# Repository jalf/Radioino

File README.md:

Radioino
========

My components for an arduino-based home automation

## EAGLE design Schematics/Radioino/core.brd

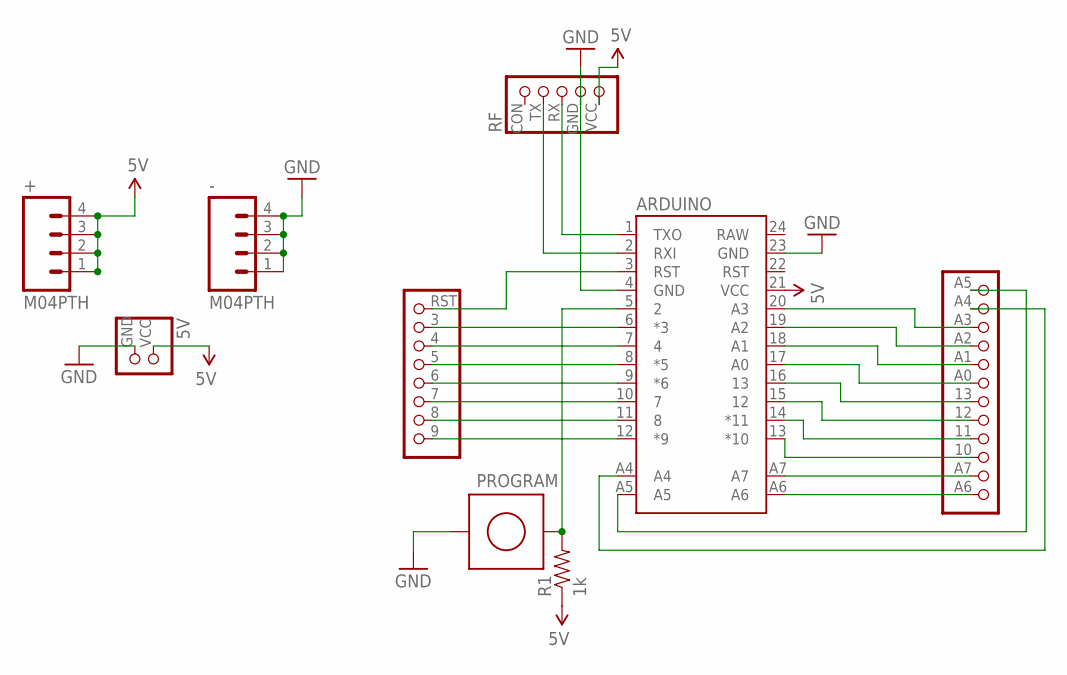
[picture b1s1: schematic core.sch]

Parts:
5V: DCPINHD-1X2; 1X02
+: M04PTH; 1X04
-: M04PTH; 1X04
ARDUINO: ARDUINO_PRO_MINI
PROGRAM: PUSHBUTTON
R1: 1k; AXIAL-0.1
RF: RFPINHD-1X5; 1X05
U$1: RIGHTPINHD-1X12; 1X12
U$2: LEFTPINHD-1X8; 1X08

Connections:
5V: 5V.VCC (1), +.1, +.2, +.3, +.4, ARDUINO.21 (VCC), R1.P$1 (1), RF.VCC (5)
GND: 5V.GND (2), -.1, -.2, -.3, -.4, ARDUINO.4 (GND), ARDUINO.23 (GND), PROGRAM.P$1, RF.GND (4)
unnamed: ARDUINO.A7, U$1.A7 (2)
unnamed: ARDUINO.A6, U$1.A6 (1)
unnamed: ARDUINO.13 (*10), U$1.10 (3)
unnamed: ARDUINO.14 (*11), U$1.11 (4)
unnamed: ARDUINO.15 (12), U$1.12 (5)
unnamed: ARDUINO.16 (13), U$1.13 (6)
unnamed: ARDUINO.17 (A0), U$1.A0 (7)
unnamed: ARDUINO.18 (A1), U$1.A1 (8)
unnamed: ARDUINO.19 (A2), U$1.A2 (9)
unnamed: ARDUINO.20 (A3), U$1.A3 (10)
unnamed: ARDUINO.A5, U$1.A5 (A7)
unnamed: ARDUINO.A4, U$1.A4 (11)
unnamed: ARDUINO.1 (TXO), RF.RX (3)
unnamed: ARDUINO.2 (RXI), RF.TX (2)
unnamed: ARDUINO.12 (*9), U$2.9 (1)
unnamed: ARDUINO.11 (8), U$2.8 (2)
unnamed: ARDUINO.10 (7), U$2.7 (3)
unnamed: ARDUINO.9 (*6), U$2.6 (4)
unnamed: ARDUINO.8 (*5), U$2.5
unnamed: ARDUINO.7 (4), U$2.4 (6)
unnamed: ARDUINO.6 (*3), U$2.3 (7)
unnamed: ARDUINO.3 (RST), U$2.RST (8)
unnamed: ARDUINO.5 (2), PROGRAM.P$2, R1.P$2 (2)

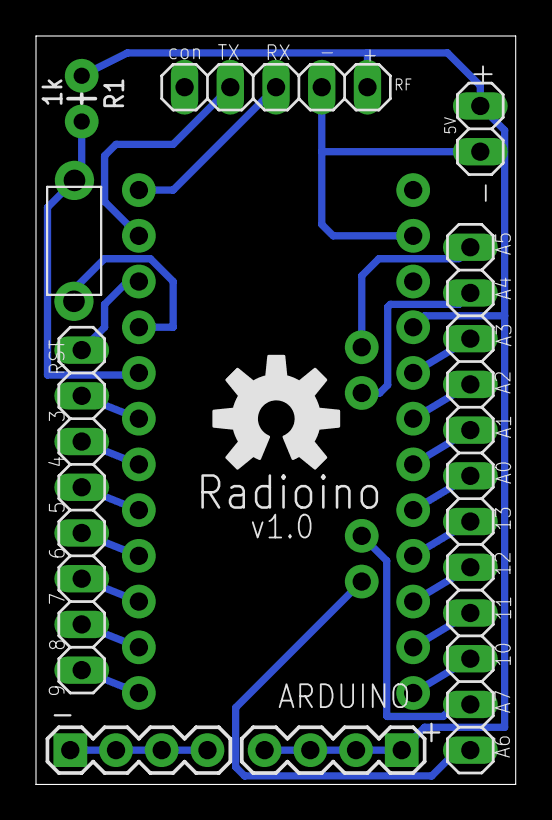
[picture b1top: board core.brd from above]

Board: 2 copper layers, 26.6 x 41.6 mm, 10 parts (0 on the bottom side), 25 nets.

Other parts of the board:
U$3: OSHW-LOGO-L

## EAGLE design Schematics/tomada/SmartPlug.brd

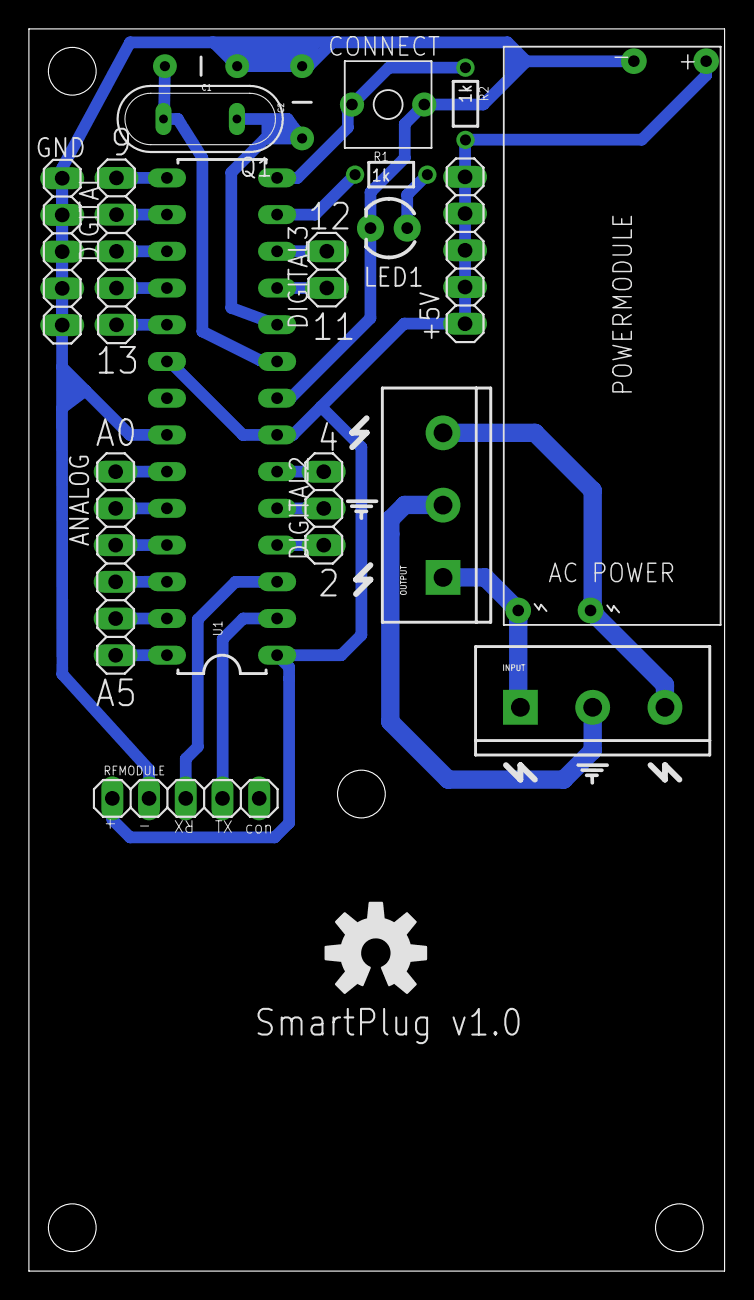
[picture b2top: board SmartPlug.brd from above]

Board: 2 copper layers, 48.1 x 85.9 mm, 23 parts (0 on the bottom side), 28 nets.

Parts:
+5V: 1X05
ANALOG: 1X06
C1, C2: 22pf; CAP-PTH-5MM
CONNECT: PUSHBUTTON6MM
DIGITAL: 1X05
DIGITAL2: 1X03
DIGITAL3: 1X02
GND: 1X05
INPUT: SCREWTERMINAL-5MM-3
LED1: LED3MM
OUTPUT: SCREWTERMINAL-5MM-3
POWERMODULE: POWER_MODULE
Q1: 16mhz; QS
R1, R2: 1k; 1/6W-RES
RFMODULE: RFPINHD-1X5; 1X05
U1: ATMEGA328P_PDIP; DIL28-3
U$1: OSHW-LOGO-L
U$2, U$3, U$4, U$5: STAND-OFF

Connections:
unnamed: RFMODULE.TX, U1.2
unnamed: RFMODULE.RX, U1.3
unnamed: LED1.A, R1.2
unnamed: +5V.1, +5V.2, +5V.3, +5V.4, +5V.5, POWERMODULE.+, R2.2, RFMODULE.VCC, U1.1, U1.7, U1.20
unnamed: C1.2, Q1.2, U1.9
unnamed: C2.1, Q1.1, U1.10
unnamed: CONNECT.P$1, R2.1, U1.14
unnamed: ANALOG.1, U1.23
unnamed: ANALOG.5, U1.27
unnamed: DIGITAL3.2, U1.11
unnamed: R1.1, U1.13
unnamed: ANALOG.2, U1.24
unnamed: ANALOG.3, U1.25
unnamed: ANALOG.6, U1.28
unnamed: DIGITAL.1, U1.15
unnamed: DIGITAL.2, U1.16
unnamed: DIGITAL.3, U1.17
unnamed: DIGITAL.4, U1.18
unnamed: DIGITAL.5, U1.19
unnamed: INPUT.3, OUTPUT.3, POWERMODULE.AC2
unnamed: INPUT.2, OUTPUT.2
unnamed: INPUT.1, OUTPUT.1, POWERMODULE.AC1
unnamed: DIGITAL2.1, U1.4
unnamed: DIGITAL2.2, U1.5
unnamed: DIGITAL2.3, U1.6
unnamed: DIGITAL3.1, U1.12
unnamed: ANALOG.4, U1.26
unnamed: C1.1, C2.2, CONNECT.P$2, GND.1, GND.2, GND.3, GND.4, GND.5, LED1.K, POWERMODULE.-, RFMODULE.GND, U1.8, U1.22

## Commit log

2014-02-08 First commit. Let's start!!
2014-02-10 Minor protocol changes
2014-02-10 Net setup mode Minor refactoring
2014-02-11 Minor activity led changes
2014-02-16 Optimizations on module response minor refactoring
2014-02-16 Change the command finalizer.
2014-02-16 CRC response check
2014-02-17 Update wallsocket to the new module class Minor fixes
2014-02-25 Update radioino.cpp
    valueSize armazena em cache o tamanho de value.length(), então não precisamos recalcular o tamanho em cada iteração.
2014-02-26 New board Added the "program" button on the board
2014-03-09 adjustments for the new pushbutton in the board
2014-06-23 Fix blink Update sample to the new hardware configuration
2014-07-10 Added the custom command callback
2014-11-11 New switch module
2014-11-12 new OBS
2014-11-12 New smartplug module
2014-11-27 New WallSocket schematic
2014-12-27 Initial ESP8266 suppport
2015-01-01 inital setup functions

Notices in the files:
parts and their libraries:
SparkFun-Resistors: Licensing: CC v3.0 Share-Alike You are welcome to use this library for commercial purposes.
